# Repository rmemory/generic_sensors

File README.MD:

The purpose of this project is to design a board containing several sensors and I/O such as temperature, light, buttons, etc. 

The initial CPU board used will be the 1bitsy. 

http://1bitsy.org/

For the first revision, a simple keyed convertor PCB will be used to access GPIO, I2C, SPI, and analog pins on the CPU. The connector will be "keyed" meaning, its designed such that the connector cannot be used with the wrong polarity.

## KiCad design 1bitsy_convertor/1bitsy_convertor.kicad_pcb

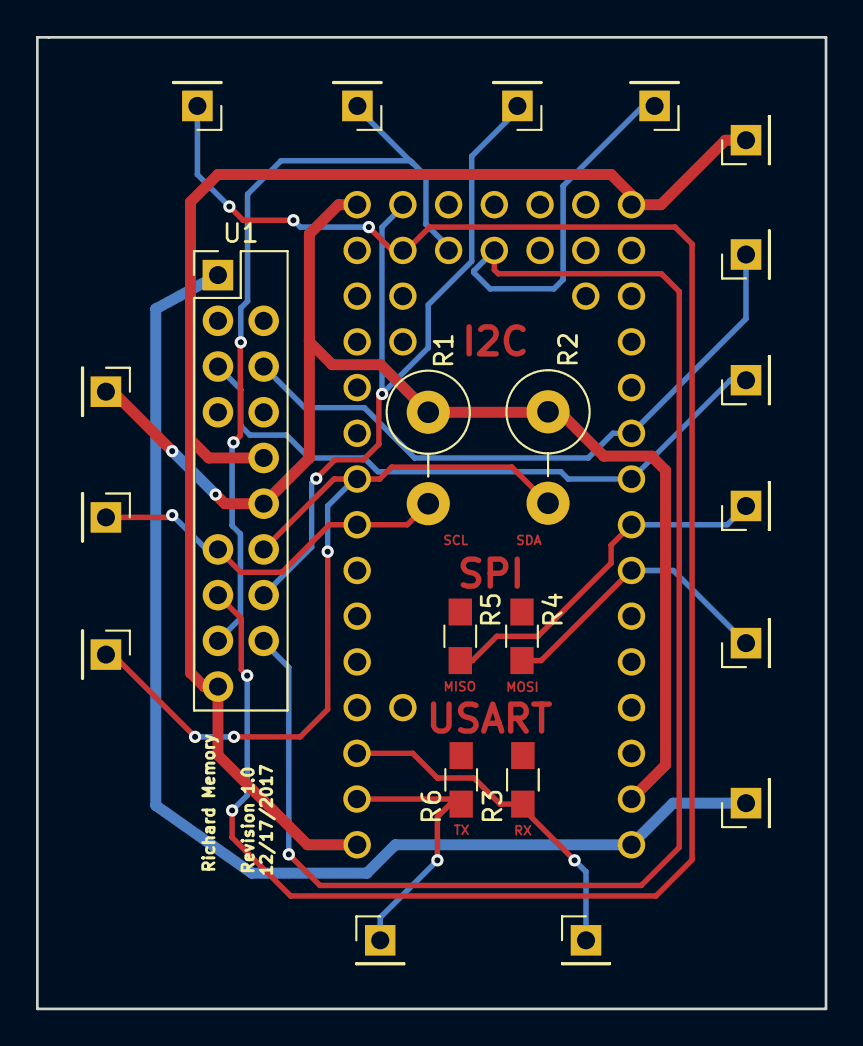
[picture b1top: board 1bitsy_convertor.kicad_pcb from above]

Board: 2 copper layers, 43.8 x 54.0 mm, 23 parts (1 on the bottom side), 20 nets.

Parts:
J1: SPI_SCK; Pin_Header_Straight_1x01_Pitch2.54mm
J2: SPI_MOSI; Pin_Header_Straight_1x01_Pitch2.54mm
J3: PWR_3.3; Pin_Header_Straight_1x01_Pitch2.54mm
J4: AIO_0; Pin_Header_Straight_1x01_Pitch2.54mm
J5: AIO_2; Pin_Header_Straight_1x01_Pitch2.54mm
J6: PWR_5V; Pin_Header_Straight_1x01_Pitch2.54mm
J7: GND; Pin_Header_Straight_1x01_Pitch2.54mm
J8: SPI_MISO; Pin_Header_Straight_1x01_Pitch2.54mm
J9: AIO_3; Pin_Header_Straight_1x01_Pitch2.54mm
J10: AIO_1; Pin_Header_Straight_1x01_Pitch2.54mm
J11: I2C_SDA; Pin_Header_Straight_1x01_Pitch2.54mm
J12: USART_TX; Pin_Header_Straight_1x01_Pitch2.54mm
J13: I2C_SCL; Pin_Header_Straight_1x01_Pitch2.54mm
J14: USART_RX; Pin_Header_Straight_1x01_Pitch2.54mm
J15: SPI_SCS; Pin_Header_Straight_1x01_Pitch2.54mm
R1, R2: 4.7k; R_Axial_DIN0414_L11.9mm_D4.5mm_P5.08mm_Vertical
R3, R4, R5, R6: 0; R_0805_HandSoldering
U1: 1bitsy_convertor; 1bitsy_convertor_pitch2.54mm
U2: 1bitsy-complete; 1bitsy

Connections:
/AIO_0: J4.1, U1.15, U2.31
/AIO_1: J10.1, U1.16, U2.32
/AIO_2: J5.1, U1.17, U2.33
/AIO_3: J9.1, U1.18, U2.35
/GND: J7.1, U1.10, U1.19, U2.1, U2.16
/I2C_SCL: J13.1, R1.2, U1.13, U2.8
/I2C_SDA: J11.1, R2.2, U1.14, U2.9
/NC: U2.4, U2.5, U2.6, U2.7, U2.10, U2.11, U2.12, U2.13, U2.14, U2.17, U2.18, U2.19, U2.20, U2.25, U2.26, U2.27, U2.28, U2.34, U2.36, U2.37, U2.38, U2.39, U2.40, U2.41, U2.42, U2.43, U2.44
/PWR_3.3: J3.1, R1.1, R2.1, U1.12, U2.15, U2.29
/PWR_5: J6.1, U1.1, U2.30
/SPI_CS: J15.1, U1.6, U2.21
/SPI_MISO: J8.1, R5.1, U2.23
/SPI_MISO_C: R5.2, U1.4
/SPI_MOSI: J2.1, R4.1, U2.24
/SPI_MOSI_C: R4.2, U1.3
/SPI_SCK: J1.1, U1.5, U2.22
/USART_RX: J14.1, R3.1, U2.3
/USART_RX_C: R3.2, U1.7
/USART_TX: J12.1, R6.1, U2.2
/USART_TX_C: R6.2, U1.8

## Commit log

2017-12-13 Commit initial, empty project
2017-12-13 Created a directory for the 1bitsy_convertor to create a project hirearchy
2017-12-13 Add README and project information to the schematic
2017-12-13 Add final schematic library component and footprint for 1bitsy convertor
2017-12-13 minor update to schematic
2017-12-14 Complete schematic for the 1 bitsy convertor
2017-12-16 Add footprint for the back of the 1bitsy
2017-12-16 Add net list
2017-12-17 First iteration of layout complete
2017-12-17 Incomplete refactoring of testing points, still need to add one for the SPI CLK and positition pads on layout
2017-12-19 layout with test points
2017-12-19 Added gerber files
